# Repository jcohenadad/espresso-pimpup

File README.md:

# Espresso pimp up ☕

DIY project to pimp up my espresso machine to display various measures

## Material

- Power
  - [MEAN WELL USA Inc. RS-15-5 AC/DC CONVERTER 5V 15W](https://www.digikey.ca/en/products/detail/mean-well-usa-inc/RS-15-5/7706168)
- Display
  - [Graphic LCD Display Module IPS (In-Plane Switching) SPI 1.69"](https://www.digikey.com/en/products/detail/seeed-technology-co-ltd/104990802/21526011)
  - [CONN HEADER SMD 8POS 1.25MM](https://www.digikey.ca/en/products/detail/hirose-electric-co-ltd/DF13C-8P-1-25V-21/3977750)
  - [8 Position (pitch 1.25mm) Cable Assembly Rectangular Socket to Socket 450.00mm](https://www.digikey.ca/en/products/detail/molex/0151340805/6198210)
  - 4x 2mm metric threading screws https://github.com/jcohenadad/espresso-pimpup/issues/42
- Temperature
  - [K Type Thermocouple Temperature Sensor](https://www.amazon.ca/MECCANIXITY-Thermocouple-Temperature-Sensor-Stainless/dp/B0C998V2DP)
  - [Thermocouple Amplifier MAX31855](https://www.amazon.ca/dp/B00SK8NDAI)

### Water level
| Item | Quantity | Description |
| ---- | -------- | ----------- |
| [FDC1004DGSR](https://www.digikey.ca/en/products/detail/texas-instruments/FDC1004DGSR/5250523) | 1 | 4-channel 16-bit capacitance-to-digital converter |
| [LCQT-MSOP10](https://www.digikey.ca/en/products/detail/aries-electronics/LCQT-MSOP10/4754589) | 1 | To create the breakout board for the FDC1004 chip |
| [WR-PHD 2.54 MM SOCKET HEADER 5 P](https://www.digikey.ca/en/products/detail/w%C3%BCrth-elektronik/61300511821/16608594) | 2 | To plug the breakout board on the main PCB |
| [C0603C104M4RACTU](https://www.digikey.ca/en/products/detail/kemet/C0603C104M4RACTU/411098) | 1 | Decoupling Capacitor |
| [RC0603FR-074K7L](https://www.digikey.ca/en/products/detail/yageo/rc0603fr-074k7l/727212) | 2 | Pull-up Resistors for I2C |

## Pictures

https://photos.app.goo.gl/eQaupZRUNoXkHYi69

## Upload/Monitor Arduino code

Using CLI (you need to adjust the correct port):

```shell
# Compile
arduino-cli compile --fqbn arduino:avr:nano ArduinoEspressoSensor/
# Upload
arduino-cli upload ArduinoEspressoSensor -b arduino:avr:nano -p /dev/cu.usbserial-BG0046HD
# Monitor
arduino-cli monitor -p /dev/cu.usbserial-BG0046HD --config 9600
```

## Calibration

Before using the setup, some calibration is needed.

### Water tank

- Activate debug mode: `DEBUG_CAPACITANCE false`
- Check capacitance values for empty and full tank.
- Enter respective values for variables `LOWER_BOUND` and `UPPER_BOUND`

### Timer

Timer for brewing duration is based on the variable `pressureThreshold`, which can be adjusted if needed.

## References

This project is inspired by the following sources:
- https://www.youtube.com/watch?v=4V0a9dfkx9Q
- https://github.com/PostModernDesign/RancilioBrain/blob/master/RancilioBrain.md
- https://github.com/urbantrout/bleeding-edge-ranciliopid/tree/master?tab=readme-ov-file
- https://clevercoffee.de/rancilio-silvia-demontage/
- https://clevercoffee.de/gaggia-classic-9480/
- https://clevercoffee.de/rancilio-silvia-e-konstantin/
- https://clevercoffee.de/rancilio-silvia-e-sebi/
- https://www.youtube.com/watch?v=AzQRCUg6E9g
- https://optimalprimate.github.io/projects/2020/11/14/coffee.html
- https://github.com/mwood77/koffie
  - https://www.seattlecoffeegear.com/cdn/shop/files/silvia-pid-installation-guide.pdf?v=8847236618586878957
- https://www.reddit.com/r/ranciliosilvia/search/?q=pid&cId=b4224602-a8c1-4eaf-a334-e28db799d089&iId=4bad28b5-60e2-4aab-9f05-2a9fabc166d9
- https://github.com/brycesub/silvia-pi?tab=readme-ov-file

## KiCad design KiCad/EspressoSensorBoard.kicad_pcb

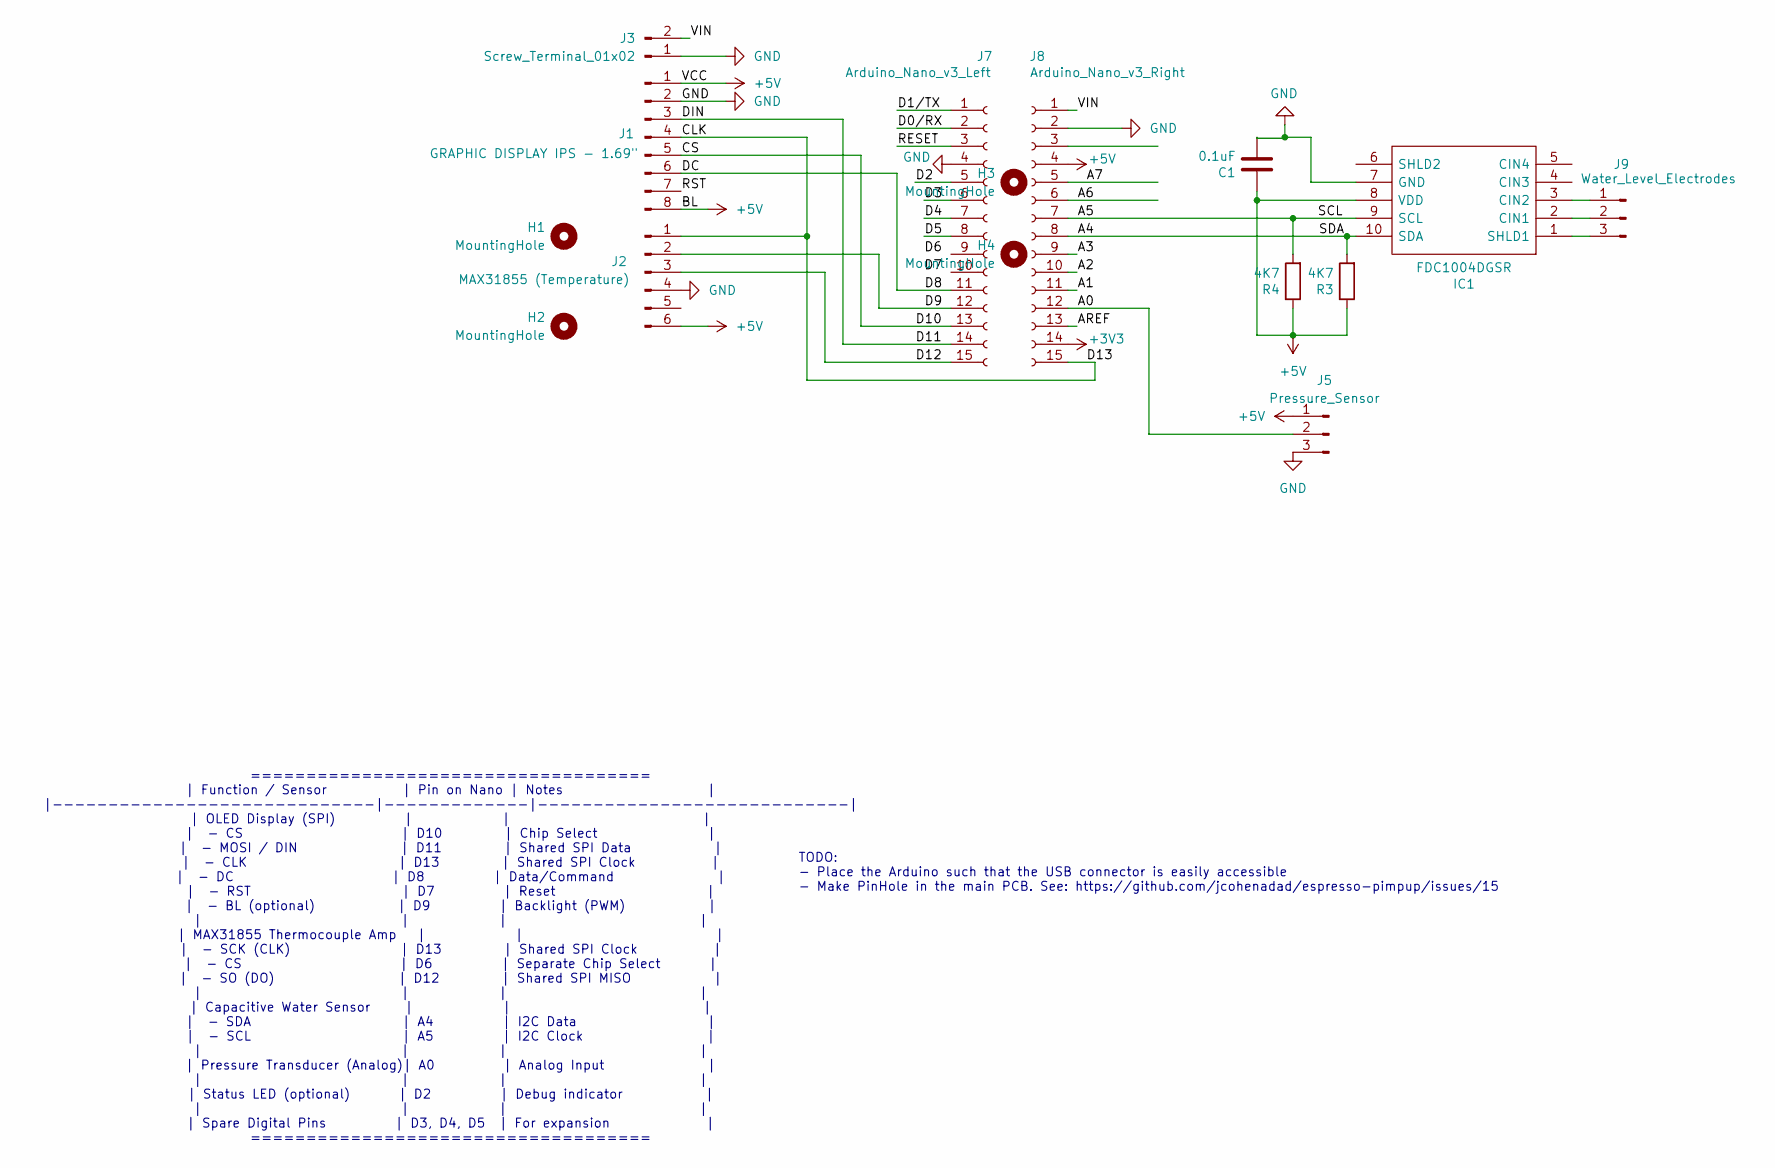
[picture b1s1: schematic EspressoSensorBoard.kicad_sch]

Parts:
C1: 0.1uF; C_0805_2012Metric_Pad1.18x1.45mm_HandSolder
H1, H2, H3, H4: MountingHole; MountingHole_2.2mm_M2
IC1: FDC1004DGSR; MSOP-10_3x3mm_P0.5mm; Mouser Part Number 595-FDC1004DGSR
J1: GRAPHIC DISPLAY IPS - 1.69"; JST_GH_BM08B-GHS-TBT_1x08-1MP_P1.25mm_Vertical
J2: MAX31855 (Temperature); PinHeader_1x06_P2.54mm_Vertical
J3: Screw_Terminal_01x02; PinHeader_1x02_P2.54mm_Vertical
J5: Pressure_Sensor; PinHeader_1x03_P2.54mm_Vertical
J7: Arduino_Nano_v3_Left; PinSocket_1x15_P2.54mm_Vertical
J8: Arduino_Nano_v3_Right; PinSocket_1x15_P2.54mm_Vertical
J9: Water_Level_Electrodes; PinHeader_1x03_P2.54mm_Vertical
R3, R4: 4K7; R_0805_2012Metric_Pad1.20x1.40mm_HandSolder

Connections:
+3V3: J8.14
+5V: C1.1, IC1.8 (VDD), J1.1, J1.8, J2.6, J5.1, J8.4, R3.1, R4.1
/A0: J5.2, J8.12
/A1: J8.11
/A2: J8.10
/A3: J8.9
/A4: IC1.10 (SDA), J8.8, R3.2
/A5: IC1.9 (SCL), J8.7, R4.2
/A6: J8.6
/A7: J8.5
/AREF: J8.13
/CLK: J1.4, J2.1, J8.15
/CS: J1.5, J7.13
/D0/RX: J7.2
/D1/TX: J7.1
/D2: J7.5
/D3: J7.6
/D4: J7.7
/D5: J7.8
/D8: J1.6, J7.11
/D9: J2.2, J7.12
/D11: J1.3, J7.14
/D12: J2.3, J7.15
/RESET: J7.3
/RST: J1.7
/VIN: J3.2, J8.1
GND: C1.2, IC1.7 (GND), J1.2, J2.4, J3.1, J5.3, J7.4, J8.2
unnamed: IC1.2 (CIN1), J9.2
unnamed: IC1.3 (CIN2), J9.1
unnamed: IC1.1 (SHLD1), J9.3

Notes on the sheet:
==================================== | Function / Sensor | Pin on Nano | Notes | |-----------------------------|-------------|----------------------------| | OLED Display (SPI) | | | | - CS | D10 | Chip Select | | - MOSI / DIN | D11 | Shared SPI Data | | - CLK | D13 | Shared SPI Clock | | - DC | D8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
TODO: - Place the Arduino such that the USB connector is easily accessible - Make PinHole in the main PCB. See: https://github.com/jcohenadad/espresso-pimpup/issues/15

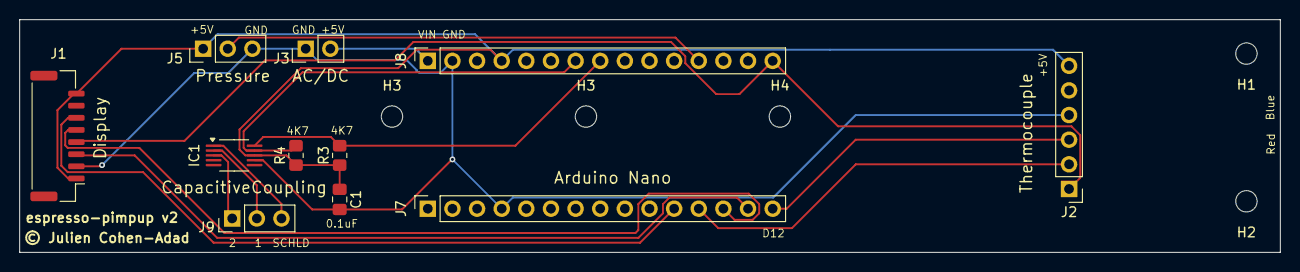
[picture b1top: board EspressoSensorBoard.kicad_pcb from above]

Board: 2 copper layers, 130.0 x 24.0 mm, 16 parts (0 on the bottom side), 15 nets.

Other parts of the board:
H3#2: MountingHoles_Rancilio; MountingHole_2.2mm_M2

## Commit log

2024-09-30 Added US
2024-09-30 Added prototype arduino code
2024-09-30 Added .gitignore
2024-09-30 Added setup.h
2024-09-30 Added placeholder for US display
2024-10-13 Added code to measure pressure
2024-10-17 Working code with temperature, pressure and distance :)
2024-10-17 Clip pressure if Voltage is below 0.5V
    Due to noise fluctuation
2024-10-17 Added water tank level in percent
2024-10-17 Fixed wrong calculation of water tank level
2024-11-14 Change digit
2024-11-14 Refactoring
2024-11-25 Changed delay
2024-12-06 Updated list of material
2024-12-19 Working prototype with new TFT 1"69' display
2024-12-19 Removed conflict between TFT display and ultrasound PIN
2024-12-19 Working display for all sensors
2024-12-19 Adding opaque background to cleanup display from previous loop
2025-04-12 Renamed file
2025-04-12 Replaced temperature sensor DB18 for thermocouple MAX31855
2025-04-15 Added cap sensor
2025-04-15 Added components
2025-04-16 Added CST python script
2025-04-16 Updated figure creation from CST
2025-04-16 Added CST project
2025-04-17 Added new CST results
2025-04-17 Added KiCad project
2025-04-28 Added KiCad files
2025-05-30 Replaced ultrasound by capacitive coupling
    WIP
2025-05-30 Added documentation for Arduino CLI
2025-05-30 Renamed Arduino folder to match INO file
    Required by Arduino for compilation
2025-05-30 Working capacitance coupling
2025-05-30 Fixed capacitance code (I think...)
2025-05-30 Cleanup
2025-06-03 Fixed PIN for pressure
2025-06-03 Reduced delay
2025-06-03 Implemented timer for brewing
2025-06-03 Added info about calibration
2025-06-03 Improves blinking after brewing
2025-06-03 Changed color for water
2025-06-10 Added pics
2025-06-11 Added min/max capacitance values for water tank
2025-06-11 removed timer for now (not working)
2025-06-20 Use SCHLD1 pin from the FDC1004 capacitive sensor
    https://github.com/jcohenadad/espresso-pimpup/issues/43
2025-06-20 Replaced screw terminal by Dupont male pins
    https://github.com/jcohenadad/espresso-pimpup/issues/38
2025-06-20 Updated PCB and Arduino code
    - Swapped D7 with D9 for easier routing
    - Removed connection to RST on the Display (should work without it)
    - Replaced connectors, notably using JST GH1.25mm for the display. https://github.com/jcohenadad/espresso-pimpup/issues/28
    - Changed 3D model for Arduino. https://github.com/jcohenadad/espresso-pimpup/issues/44
    - Connected pin to shielding on FDC1004. https://github.com/jcohenadad/espresso-pimpup/issues/41
2025-06-20 Minor modifs on the Kicad PCD
2025-06-20 Fixed missing connection
2025-06-20 Fixed arduino connector
2025-09-21 Add JST connector to README components list
2025-09-22 Add threading screws to display components list
    Added 4x 2mm metric threading screws to the display section.
2025-09-22 Update README with link for threading screws
2026-04-05 Updated schematic
2026-04-05 Added file for quick compile
2026-04-05 Updated list
2026-04-11 Calibrated water level-- added out-of-bound fix
2026-04-11 Fixed inverted water level percentage
2026-04-11 Updated display
    Related to #46

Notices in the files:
KiCad/EspressoSensorBoard.kicad_pcb:
© Julien Cohen-Adad
